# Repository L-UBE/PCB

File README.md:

# PCB

the pcb for cuwube

v1 - initial pcb from fall quarter

v2 - adding in voltage regulator changes

v3 - with the 0 ohm resistor for the voltage regulator

v4 - removed bluetooth module, opened pins

v5 - changed parts for JLC

v6 - third iteration of pcb, for cube

v7 - third iteration of pcb, for glove

v8 - new pcb for tri-state buffers

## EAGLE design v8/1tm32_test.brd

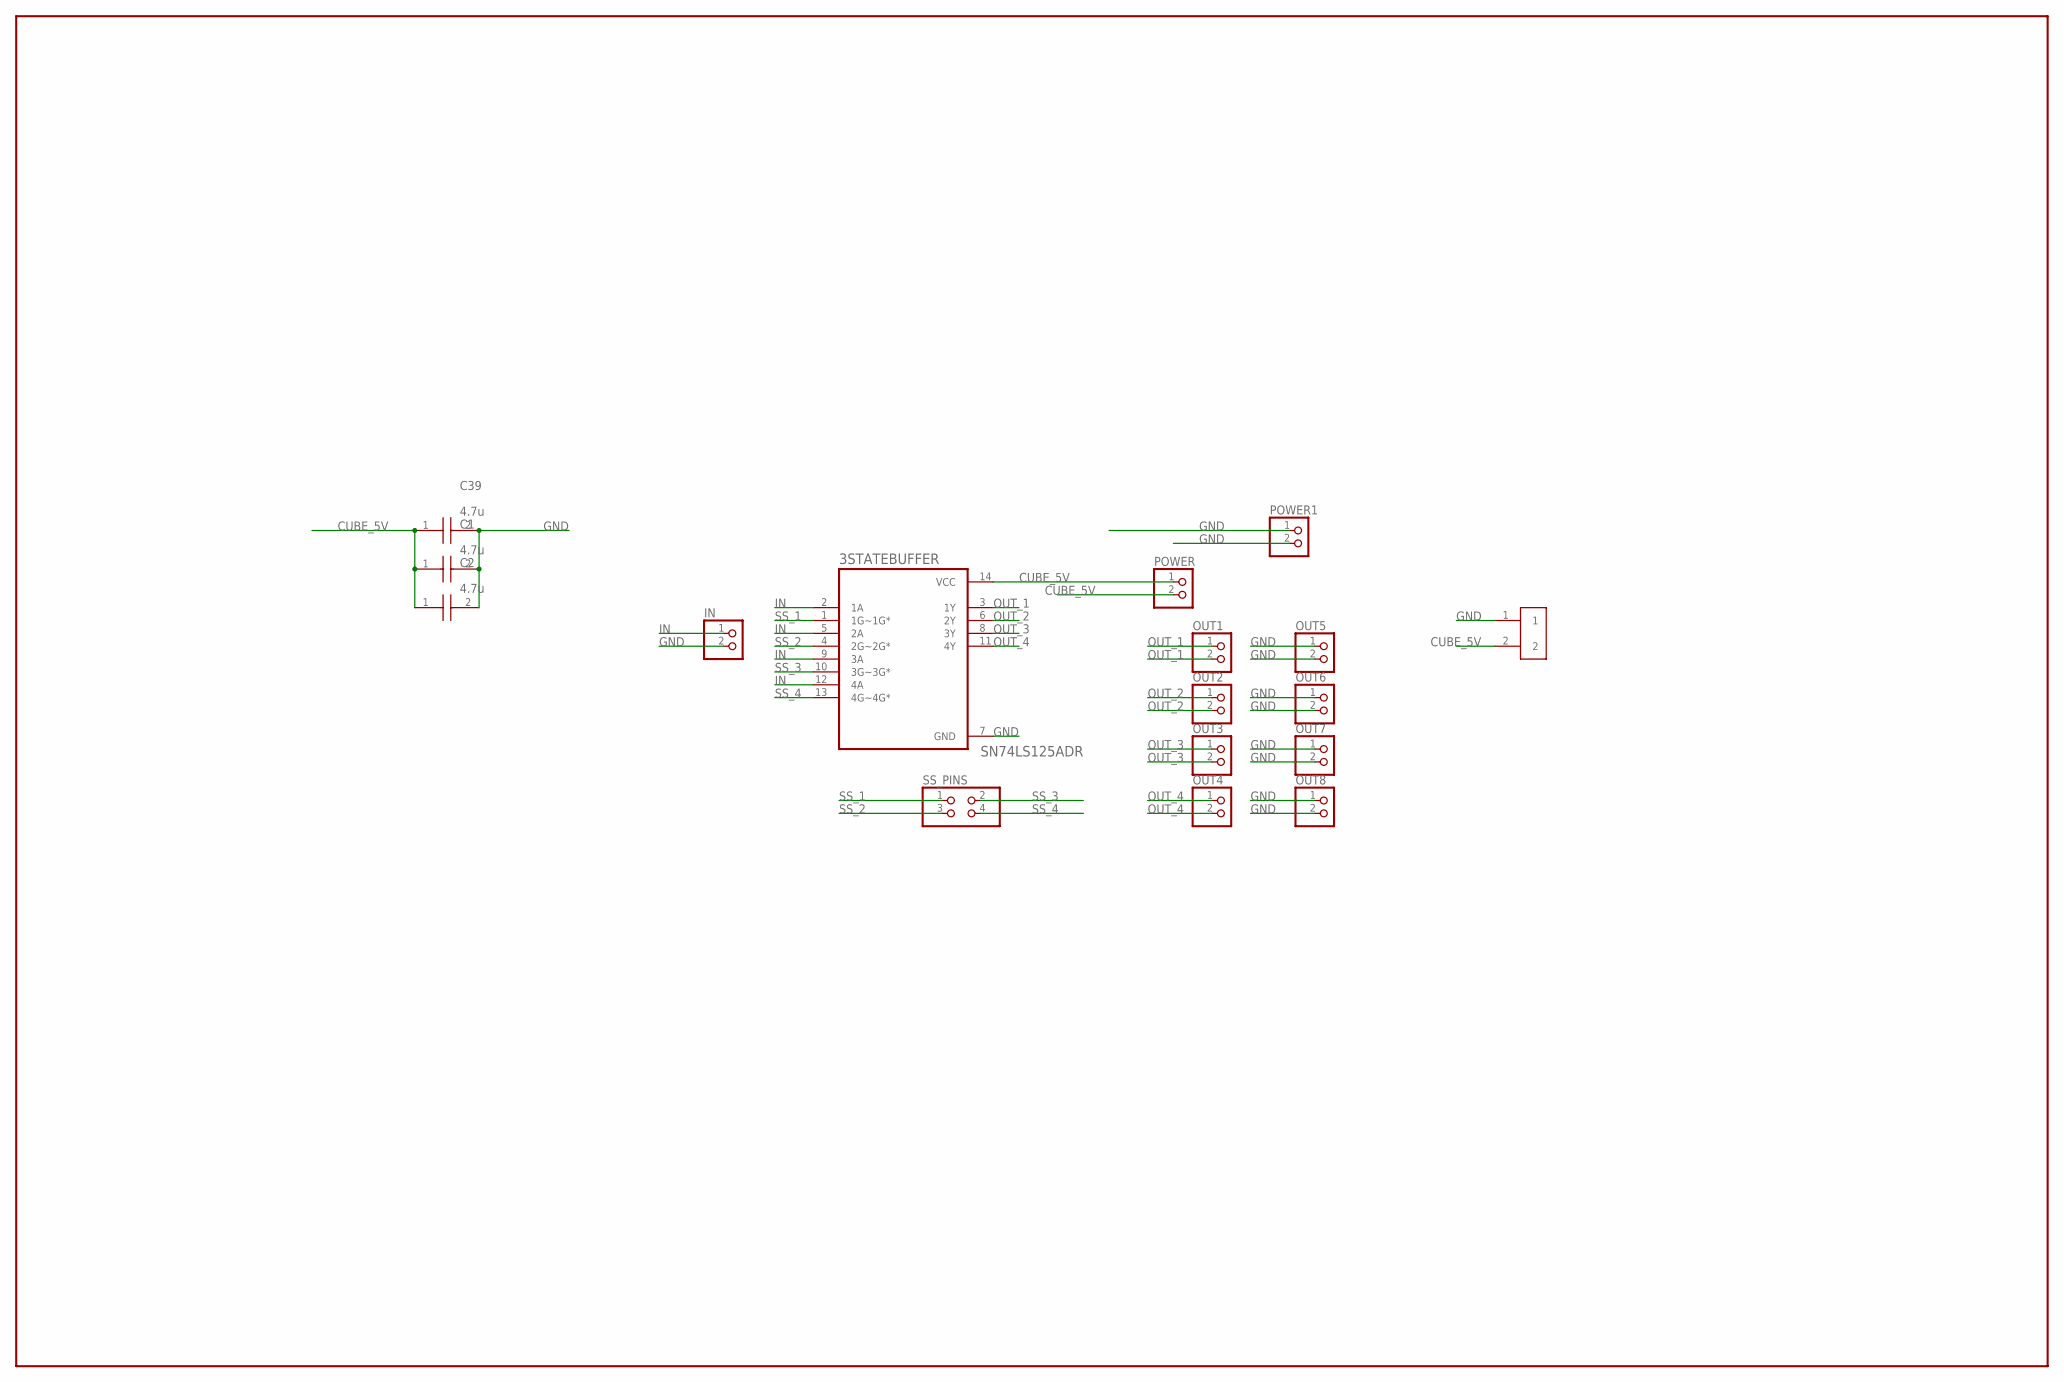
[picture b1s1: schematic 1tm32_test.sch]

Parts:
3STATEBUFFER: SN74LS125ADR; SOIC127P600X175-14N
C1, C2, C39: 4.7u; CAPC2012X145N
IN: PINHD-1X2; 1X02
J1: 1935161; PHOENIX_1935161
OUT1, OUT2, OUT3, OUT4, OUT5, OUT6, OUT7, OUT8: PINHD-1X2; 1X02
POWER, POWER1: PINHD-1X2; 1X02
SS_PINS: PINHD-2X2; 2X02

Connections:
CUBE_5V: 3STATEBUFFER.14 (VCC), C1.1, C2.1, C39.1, J1.2, POWER.1, POWER.2
GND: 3STATEBUFFER.7 (GND), C1.2, C2.2, C39.2, IN.2, J1.1, OUT5.1, OUT5.2, OUT6.1, OUT6.2, OUT7.1, OUT7.2, OUT8.1, OUT8.2, POWER1.1, POWER1.2
IN: 3STATEBUFFER.2 (1A), 3STATEBUFFER.5 (2A), 3STATEBUFFER.9 (3A), 3STATEBUFFER.12 (4A), IN.1
OUT_1: 3STATEBUFFER.3 (1Y), OUT1.1, OUT1.2
OUT_2: 3STATEBUFFER.6 (2Y), OUT2.1, OUT2.2
OUT_3: 3STATEBUFFER.8 (3Y), OUT3.1, OUT3.2
OUT_4: 3STATEBUFFER.11 (4Y), OUT4.1, OUT4.2
SS_1: 3STATEBUFFER.1 (1G~1G*), SS_PINS.1
SS_2: 3STATEBUFFER.4 (2G~2G*), SS_PINS.3
SS_3: 3STATEBUFFER.10 (3G~3G*), SS_PINS.2
SS_4: 3STATEBUFFER.13 (4G~4G*), SS_PINS.4

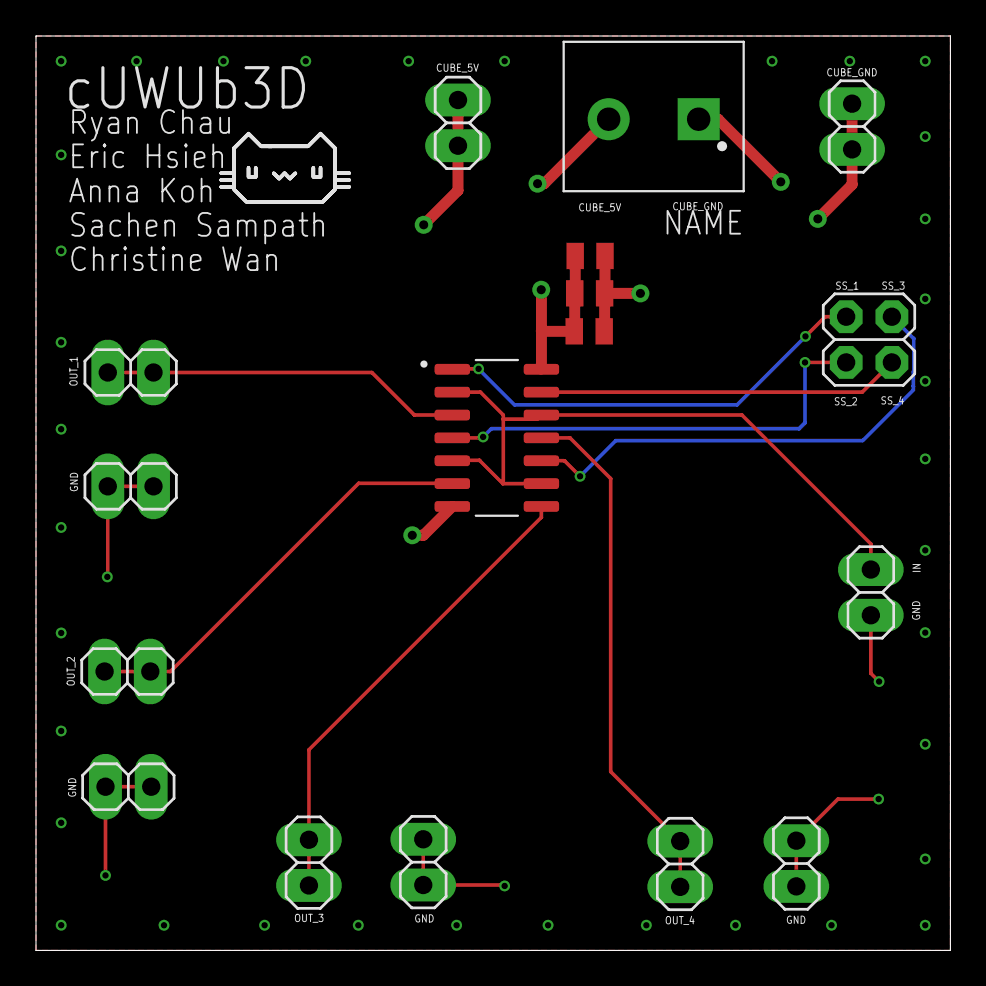
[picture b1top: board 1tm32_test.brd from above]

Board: 4 copper layers, 50.8 x 50.8 mm, 17 parts (0 on the bottom side), 11 nets.

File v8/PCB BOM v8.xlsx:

Comment | Designator | Footprint | JLCPCB Part # | Description
PINHD-1X2 | IN, OUT1, OUT2, OUT3, OUT4, OUT5, OUT6, OUT7, OUT8, POWER, POWER1 | 1X02 | C49661 | PIN HEADER
PINHD-2X2 | SS_PINS | 2X02 | C92273 | PIN HEADER
1935161.0 | J1 | PHOENIX_1935161 | C395882 | Conn Terminal Blocks 2 POS 5mm Solder ST Thru-Hole 16A Check availability
GRT21BC71H475KE13L | C1, C2, C39 | CAPC2012X145N | C520074 | GRT21BC71H475KE13_ (0805, X7S:EIA, 4.7uF, DC50V)
SN74LS125ADR | 3STATEBUFFER | SOIC127P600X175-14N | C7734 | Tri-state buffer

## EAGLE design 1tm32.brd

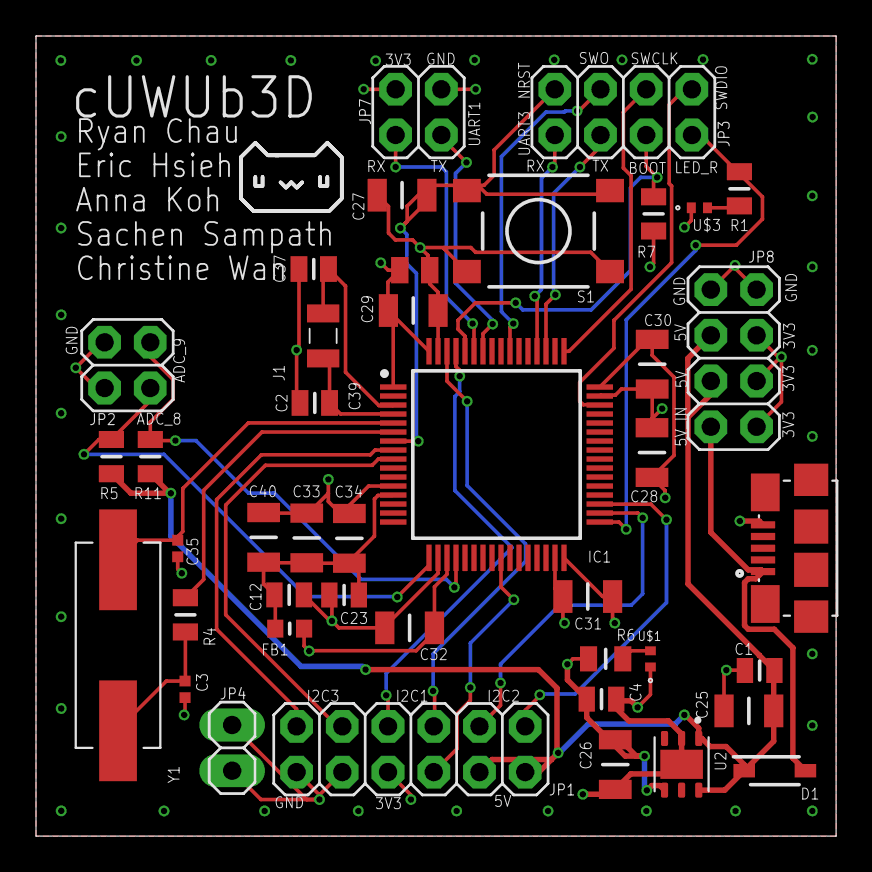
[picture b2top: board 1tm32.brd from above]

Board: 4 copper layers, 44.5 x 44.5 mm, 42 parts (0 on the bottom side), 31 nets.

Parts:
C1, C4, C12, C23: 1u; CAPC2012X95N
C2, C37: 4.7p; CAPC2012X100N
C3, C35: 20p; CAPC1005X55N
C25, C26, C27, C28, C29, C30, C31, C32, C33, C34: 100n; CAPC3216X180N
C39: 4.7u; CAPC2012X145N
C40: 10n; CAPC3216X180N
D1: 1N5819HW-7-F_1N5819HW-7-F; 1N5819HW-7-F_SOD3716X145N
FB1: BK1608HS601-T; BEADC1608X95N
IC1: STM32L412RBT6; QFP50P1200X1200X160-64N
J1: DST310S_32.768KHZ; DST310S_32.768KHZ_DST310S32768KHZ
J2: 10118192-0001LF; AMPHENOL_10118192-0001LF
JP1: 2X06
JP2, JP7: 2X02
JP3, JP8: 2X04
JP4: 1X02
R1, R6, R7: 1K; RESC2012X60N
R4: 220; RESC2012X60N
R5, R11: 10K; RESC2012X60N
S1: SWITCH-TACT_DTSM-6
U2: LD39050PU33R; SON95P300X300X100-7N
U$1, U$3: LED_R; LED_SML-P11UTT86R
Y1: 8MHz; XTAL_ABLS-8.000MHZ-B2-T

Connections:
3V3: C4.2, C26.2, C28.1, C29.1, C30.1, C31.1, C32.1, C39.1, FB1.2, IC1.1, IC1.19, IC1.32, IC1.48, IC1.64, JP1.5, JP7.2, JP8.4, JP8.6, JP8.8, R6.2, U2.4
5V: C1.2, C25.2, D1.1, JP1.9, JP1.11, JP8.3, JP8.5, R5.1, R11.1, U2.1, U2.6
5V_IN: D1.2, J2.1, JP8.7
ADC1_IN9: IC1.20, JP2.2, R11.2
ADC2_IN8: IC1.17, JP2.4, R5.2
BOOT0: IC1.60, JP3.5, R7.1
GND: C1.1, C2.2, C3.2, C4.1, C12.2, C23.2, C25.1, C26.1, C27.1, C28.2, C29.2, C30.2, C31.2, C32.2, C33.2, C34.2, C35.2, C37.2, C39.2, C40.2, IC1.12, IC1.18, IC1.31, IC1.47, IC1.63, J2.5, JP1.1, JP1.3, JP2.1, JP2.3, JP4.1, JP4.2, JP7.4, JP8.1, JP8.2, R7.2, S1.3, S1.4, U2.2, U2.7, U$1.C, U$3.C
I2C1_SCL: IC1.61, JP1.6
I2C1_SDA: IC1.62, JP1.8
I2C2_SCL: IC1.34, JP1.10
I2C2_SDA: IC1.35, JP1.12
I2C3_SCL: IC1.8, JP1.2
I2C3_SDA: IC1.9, JP1.4
LED_R: IC1.33, JP3.7, R1.2
unnamed: R1.1, U$3.A
unnamed: C3.1, R4.2, Y1.1
unnamed: R6.1, U$1.A
NRST: C27.2, IC1.7, JP3.2, S1.1, S1.2
PC5: IC1.25, JP1.7
PC14-OSC32-IN: C37.1, IC1.3, J1.1
PC15-OSC32-OUT: C2.1, IC1.4, J1.2
PH0-OSC-IN: C35.1, IC1.5, Y1.2
PH1-OSC-OUT: IC1.6, R4.1
SWCLK: IC1.49, JP3.6
SWDIO: IC1.46, JP3.8
SWO: IC1.55, JP3.4
USART1_RX: IC1.59, JP7.1
USART1_TX: IC1.58, JP7.3
USART3_RX: IC1.52, JP3.1
USART3_TX: IC1.51, JP3.3
VDDA/VREF+: C12.1, C23.1, C33.1, C34.1, C40.1, FB1.1, IC1.13

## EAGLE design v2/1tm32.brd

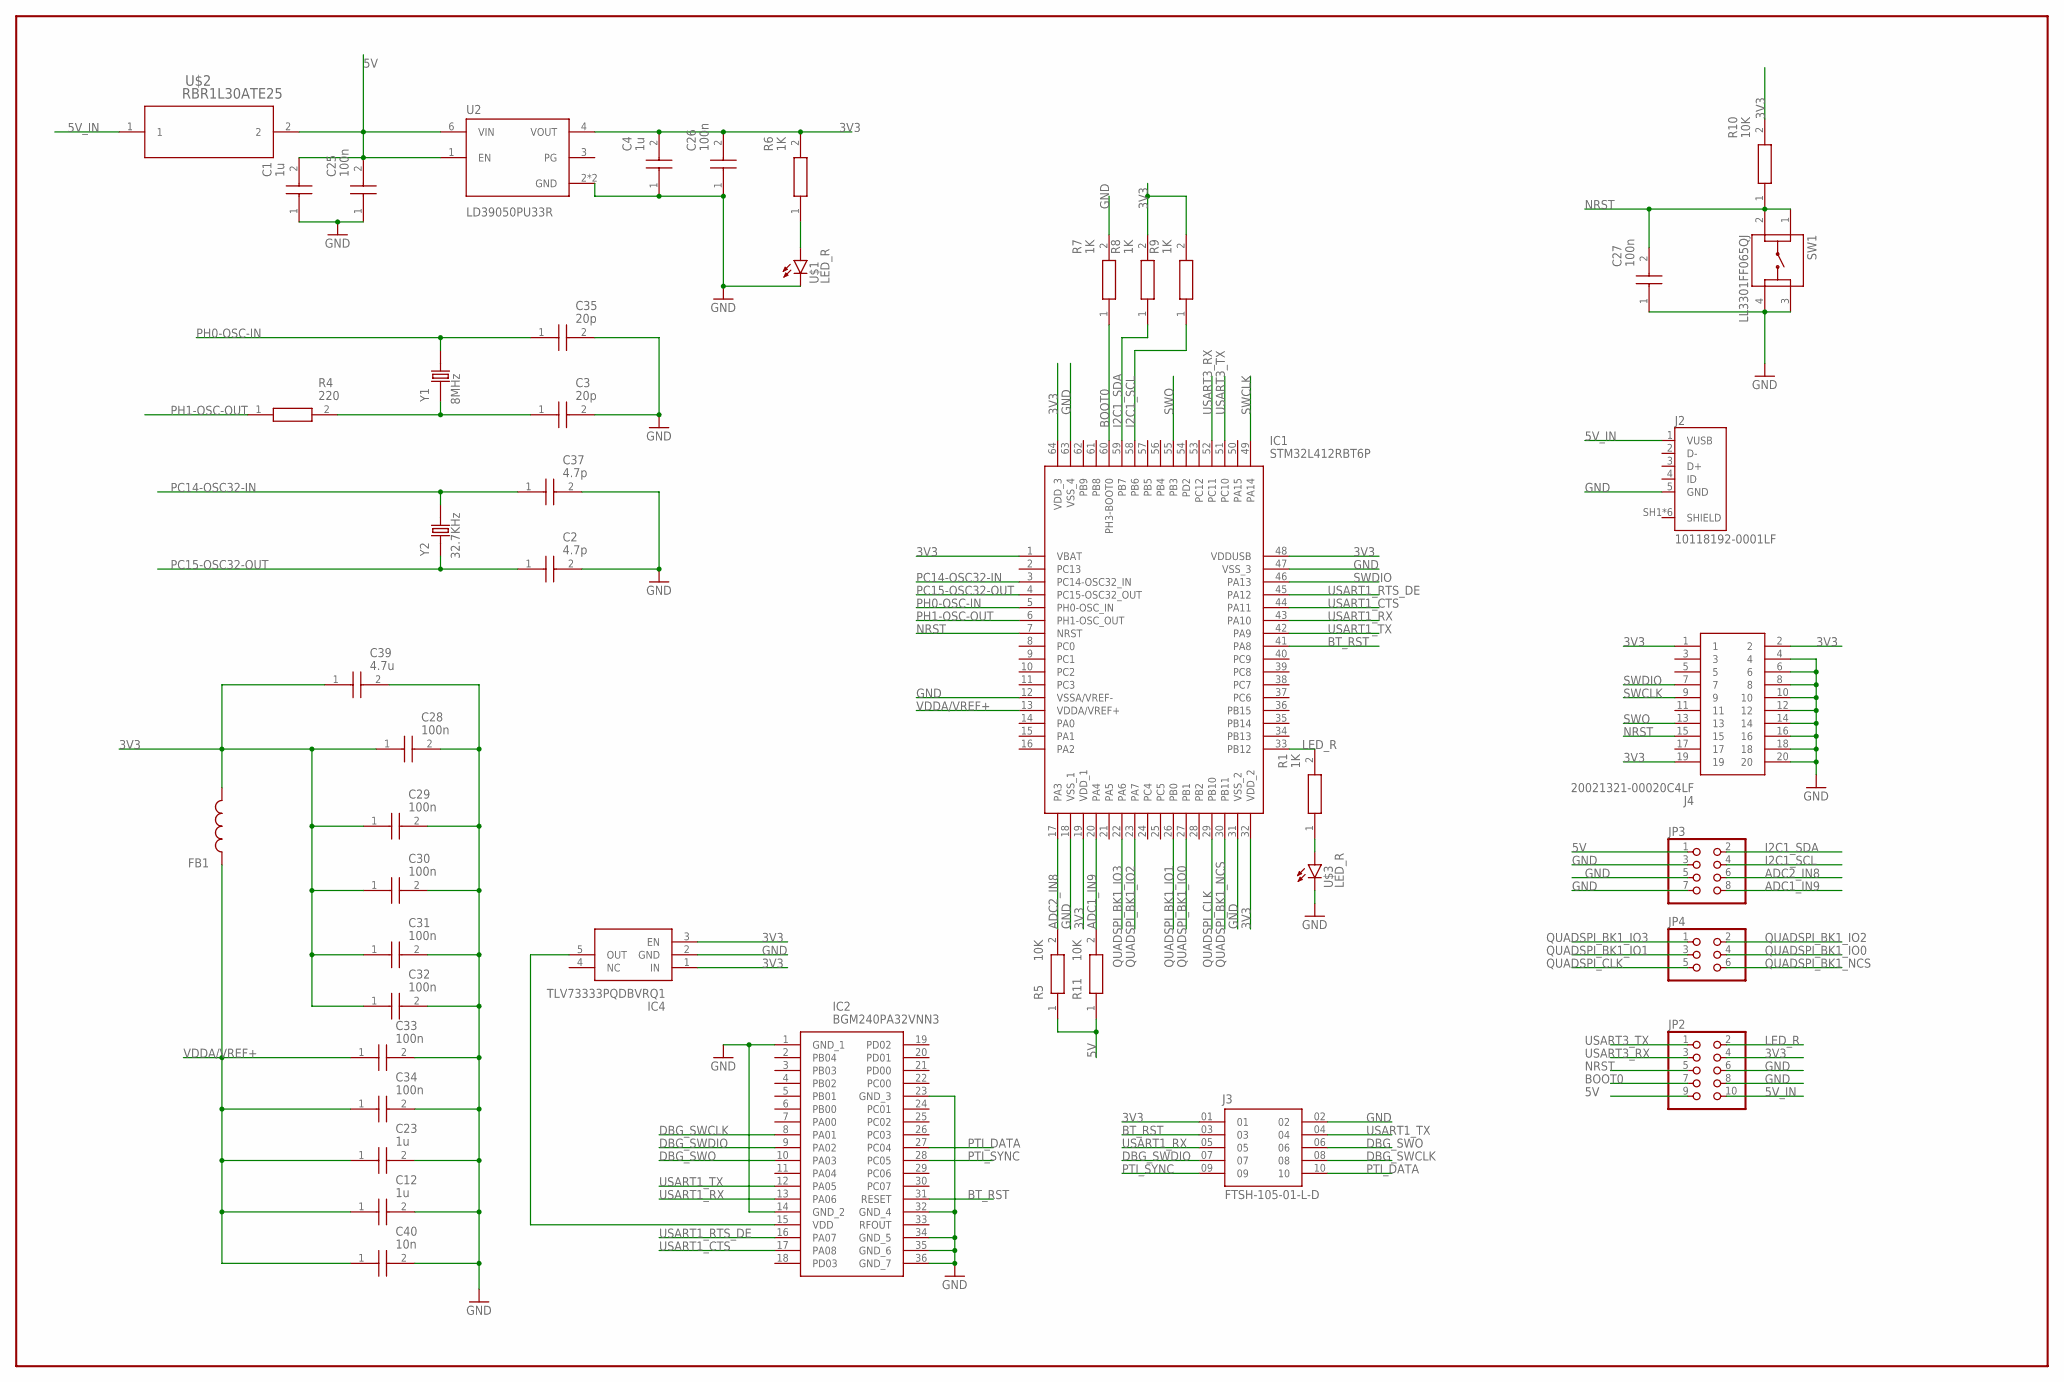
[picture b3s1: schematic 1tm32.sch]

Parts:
C1, C4, C12, C23: 1u; CAPC2012X95N
C2, C37: 4.7p; CAPC2012X100N
C3, C35: 20p; CAPC2012X100N
C25, C26, C27, C28, C29, C30, C31, C32, C33, C34: 100n; CAPC3216X180N
C39: 4.7u; CAPC2012X145N
C40: 10n; CAPC3216X180N
FB1: BK1608HS601-T; BEADC1608X95N
IC1: STM32L412RBT6P; QFP50P1200X1200X160-64N
IC2: BGM240PA32VNN3
IC4: TLV73333PQDBVRQ1; SOT95P280X145-5N
J2: 10118192-0001LF; AMPHENOL_10118192-0001LF
J3: FTSH-105-01-L-D; SAMTEC_FTSH-105-01-L-D
J4: 20021321-00020C4LF; 2002132100020C4LF
JP2: PINHD-2X5; 2X05
JP3: PINHD-2X4; 2X04
JP4: PINHD-2X3; 2X03
R1, R6, R7, R8, R9: 1K; RESC2012X60N
R4: 220; RESC2012X60N
R5, R10, R11: 10K; RESC2012X60N
SW1: LL3301FF065QJ
U2: LD39050PU33R; SON95P300X300X100-7N
U$1, U$3: LED_R; LED_SML-P11UTT86R
U$2: RBR1L30ATE25; DIO_RBR1L30_ROM
Y1: 8MHz; XTAL_ABLS-8.000MHZ-B2-T
Y2: 32.7KHz; XTAL_ECS-.327-12.5-12QS-TR

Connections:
3V3: C4.2, C26.2, C28.1, C29.1, C30.1, C31.1, C32.1, C39.1, FB1.2, IC1.1 (VBAT), IC1.19 (VDD_1), IC1.32 (VDD_2), IC1.48 (VDDUSB), IC1.64 (VDD_3), IC4.1 (IN), IC4.3 (EN), J3.01, J4.1, J4.2, J4.19, JP2.4, R6.2, R8.2, R9.2, R10.2, U2.4 (VOUT)
5V: C1.2, C25.2, JP2.9, JP3.1, R5.1, R11.1, U2.1 (EN), U2.6 (VIN), U$2.2
5V_IN: J2.1 (VUSB), JP2.10, U$2.1
ADC1_IN9: IC1.20 (PA4), JP3.8, R11.2
ADC2_IN8: IC1.17 (PA3), JP3.6, R5.2
BOOT0: IC1.60 (PH3-BOOT0), JP2.7, R7.1
BT_RST: IC1.41 (PA8), IC2.31 (RESET), J3.03
DBG_SWCLK: IC2.8 (PA01), J3.08
DBG_SWDIO: IC2.9 (PA02), J3.07
DBG_SWO: IC2.10 (PA03), J3.06
GND: C1.1, C2.2, C3.2, C4.1, C12.2, C23.2, C25.1, C26.1, C27.1, C28.2, C29.2, C30.2, C31.2, C32.2, C33.2, C34.2, C35.2, C37.2, C39.2, C40.2, IC1.12 (VSSA/VREF-), IC1.18 (VSS_1), IC1.31 (VSS_2), IC1.47 (VSS_3), IC1.63 (VSS_4), IC2.1 (GND_1), IC2.14 (GND_2), IC2.23 (GND_3), IC2.32 (GND_4), IC2.34 (GND_5), IC2.35 (GND_6), IC2.36 (GND_7), IC4.2 (GND), J2.5 (GND), J3.02, J4.4, J4.6, J4.8, J4.10, J4.12, J4.14, J4.16, J4.18, J4.20, JP2.6, JP2.8, JP3.3, JP3.5, JP3.7, R7.2, SW1.3, SW1.4, U2.2 (GND), U2.7 (GND), U$1.C, U$3.C
I2C1_SCL: IC1.58 (PB6), JP3.4, R9.1
I2C1_SDA: IC1.59 (PB7), JP3.2, R8.1
LED_R: IC1.33 (PB12), JP2.2, R1.2
unnamed: R1.1, U$3.A
unnamed: C3.1, R4.2, Y1.1
unnamed: IC2.15 (VDD), IC4.5 (OUT)
unnamed: R6.1, U$1.A
NRST: C27.2, IC1.7 (NRST), J4.15, JP2.5, R10.1, SW1.1, SW1.2
PC14-OSC32-IN: C37.1, IC1.3 (PC14-OSC32_IN), Y2.2
PC15-OSC32-OUT: C2.1, IC1.4 (PC15-OSC32_OUT), Y2.1
PH0-OSC-IN: C35.1, IC1.5 (PH0-OSC_IN), Y1.2
PH1-OSC-OUT: IC1.6 (PH1-OSC_OUT), R4.1
PTI_DATA: IC2.27 (PC04), J3.10
PTI_SYNC: IC2.28 (PC05), J3.09
QUADSPI_BK1_IO0: IC1.27 (PB1), JP4.4
QUADSPI_BK1_IO1: IC1.26 (PB0), JP4.3
QUADSPI_BK1_IO2: IC1.23 (PA7), JP4.2
QUADSPI_BK1_IO3: IC1.22 (PA6), JP4.1
QUADSPI_BK1_NCS: IC1.30 (PB11), JP4.6
QUADSPI_CLK: IC1.29 (PB10), JP4.5
SWCLK: IC1.49 (PA14), J4.9
SWDIO: IC1.46 (PA13), J4.7
SWO: IC1.55 (PB3), J4.13
USART1_CTS: IC1.44 (PA11), IC2.17 (PA08)
USART1_RTS_DE: IC1.45 (PA12), IC2.16 (PA07)
USART1_RX: IC1.43 (PA10), IC2.13 (PA06), J3.05
USART1_TX: IC1.42 (PA9), IC2.12 (PA05), J3.04
USART3_RX: IC1.52 (PC11), JP2.3
USART3_TX: IC1.51 (PC10), JP2.1
VDDA/VREF+: C12.1, C23.1, C33.1, C34.1, C40.1, FB1.1, IC1.13 (VDDA/VREF+)

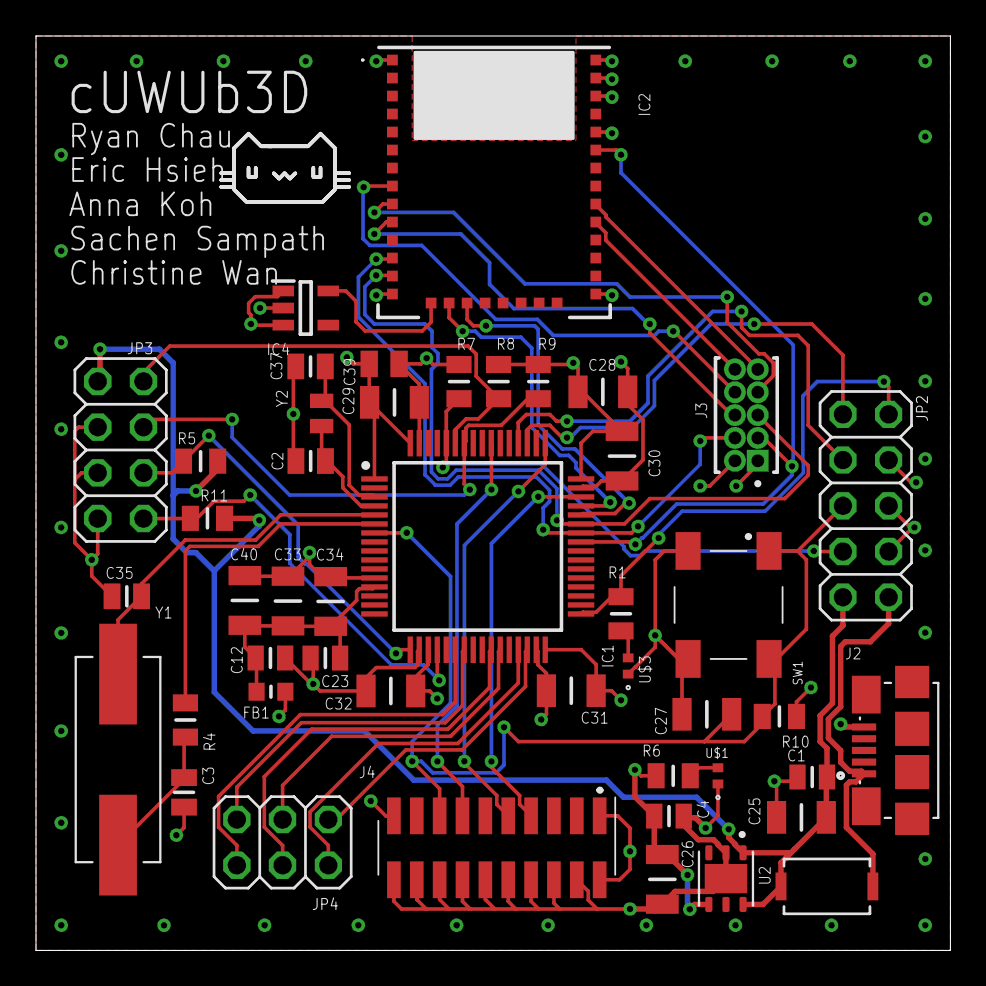
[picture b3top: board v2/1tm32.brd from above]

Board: 4 copper layers, 50.8 x 50.8 mm, 46 parts (0 on the bottom side), 41 nets.

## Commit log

2022-12-02 PCB files upload
2022-12-05 layout completed
2022-12-07 add gnd vias and change adc resistors
2022-12-07 add subfolder
2022-12-07 add to subfolder
2023-01-11 updated the Schottky diode to RBR1L30ATE25
    datasheet: https://www.mouser.com/datasheet/2/348/ROHM_S_A0008995718_1-2562906.pdf
2023-01-13 changed errors
2023-01-18 cloning before adding in voltage regulator
2023-01-18 cloning before voltage regulator
2023-01-18 add voltage regulator version
2023-01-18 move file into directory
2023-01-18 move file to directory
2023-01-19 changed voltage regulator
    previous one caused clearance issues with the wires
2023-01-25 added 0 ohm resistor
2023-01-25 Rename 1tm32.brd to v3/1tm32.brd
2023-01-25 Rename 1tm32.sch to v3/1tm32.sch
2023-03-09 Rename 1tm32.brd to v4/1tm32.brd
2023-03-09 Rename 1tm32.sch to v4/1tm32.sch
2023-03-10 added labels for header pins
2023-03-11 modified i2c headers
    removed resistors
    changed 3v3 pins to gpio pins
2023-03-11 moved some wires around
2023-03-16 moved wire around to space for pwm wave
2023-03-16 moved a via
2023-03-16 moved wires around to meet design rules for JLC
2023-03-17 changed parts for jlc
2023-03-17 Rename 1tm32.brd to v5/1tm32.brd
2023-03-17 Rename 1tm32.sch to v5/1tm32.sch
2023-03-17 removed resistor for switch
2023-03-17 moved wires around
2023-04-27 pcb version for cube
2023-04-27 Rename 1tm32.brd to v6/1tm32.brd
2023-04-27 Rename 1tm32.sch to v6/1tm32.sch
2023-04-27 added labels for pins
2023-04-28 made changes to traces
2023-05-01 Rename 1tm32.brd to v7/1tm32.brd
2023-05-01 Rename 1tm32.sch to v7/1tm32.sch
2023-05-01 buffer circuit
2023-05-01 v8 update

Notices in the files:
parts and their libraries:
RBR1L30ATE25: COPYRIGHT: Copyright (C) 2023 Ultra Librarian. All rights reserved.
